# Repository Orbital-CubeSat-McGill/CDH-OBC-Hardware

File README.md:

# CDH-OBC-Hardware
On Board Computer for Command and Data Handling.

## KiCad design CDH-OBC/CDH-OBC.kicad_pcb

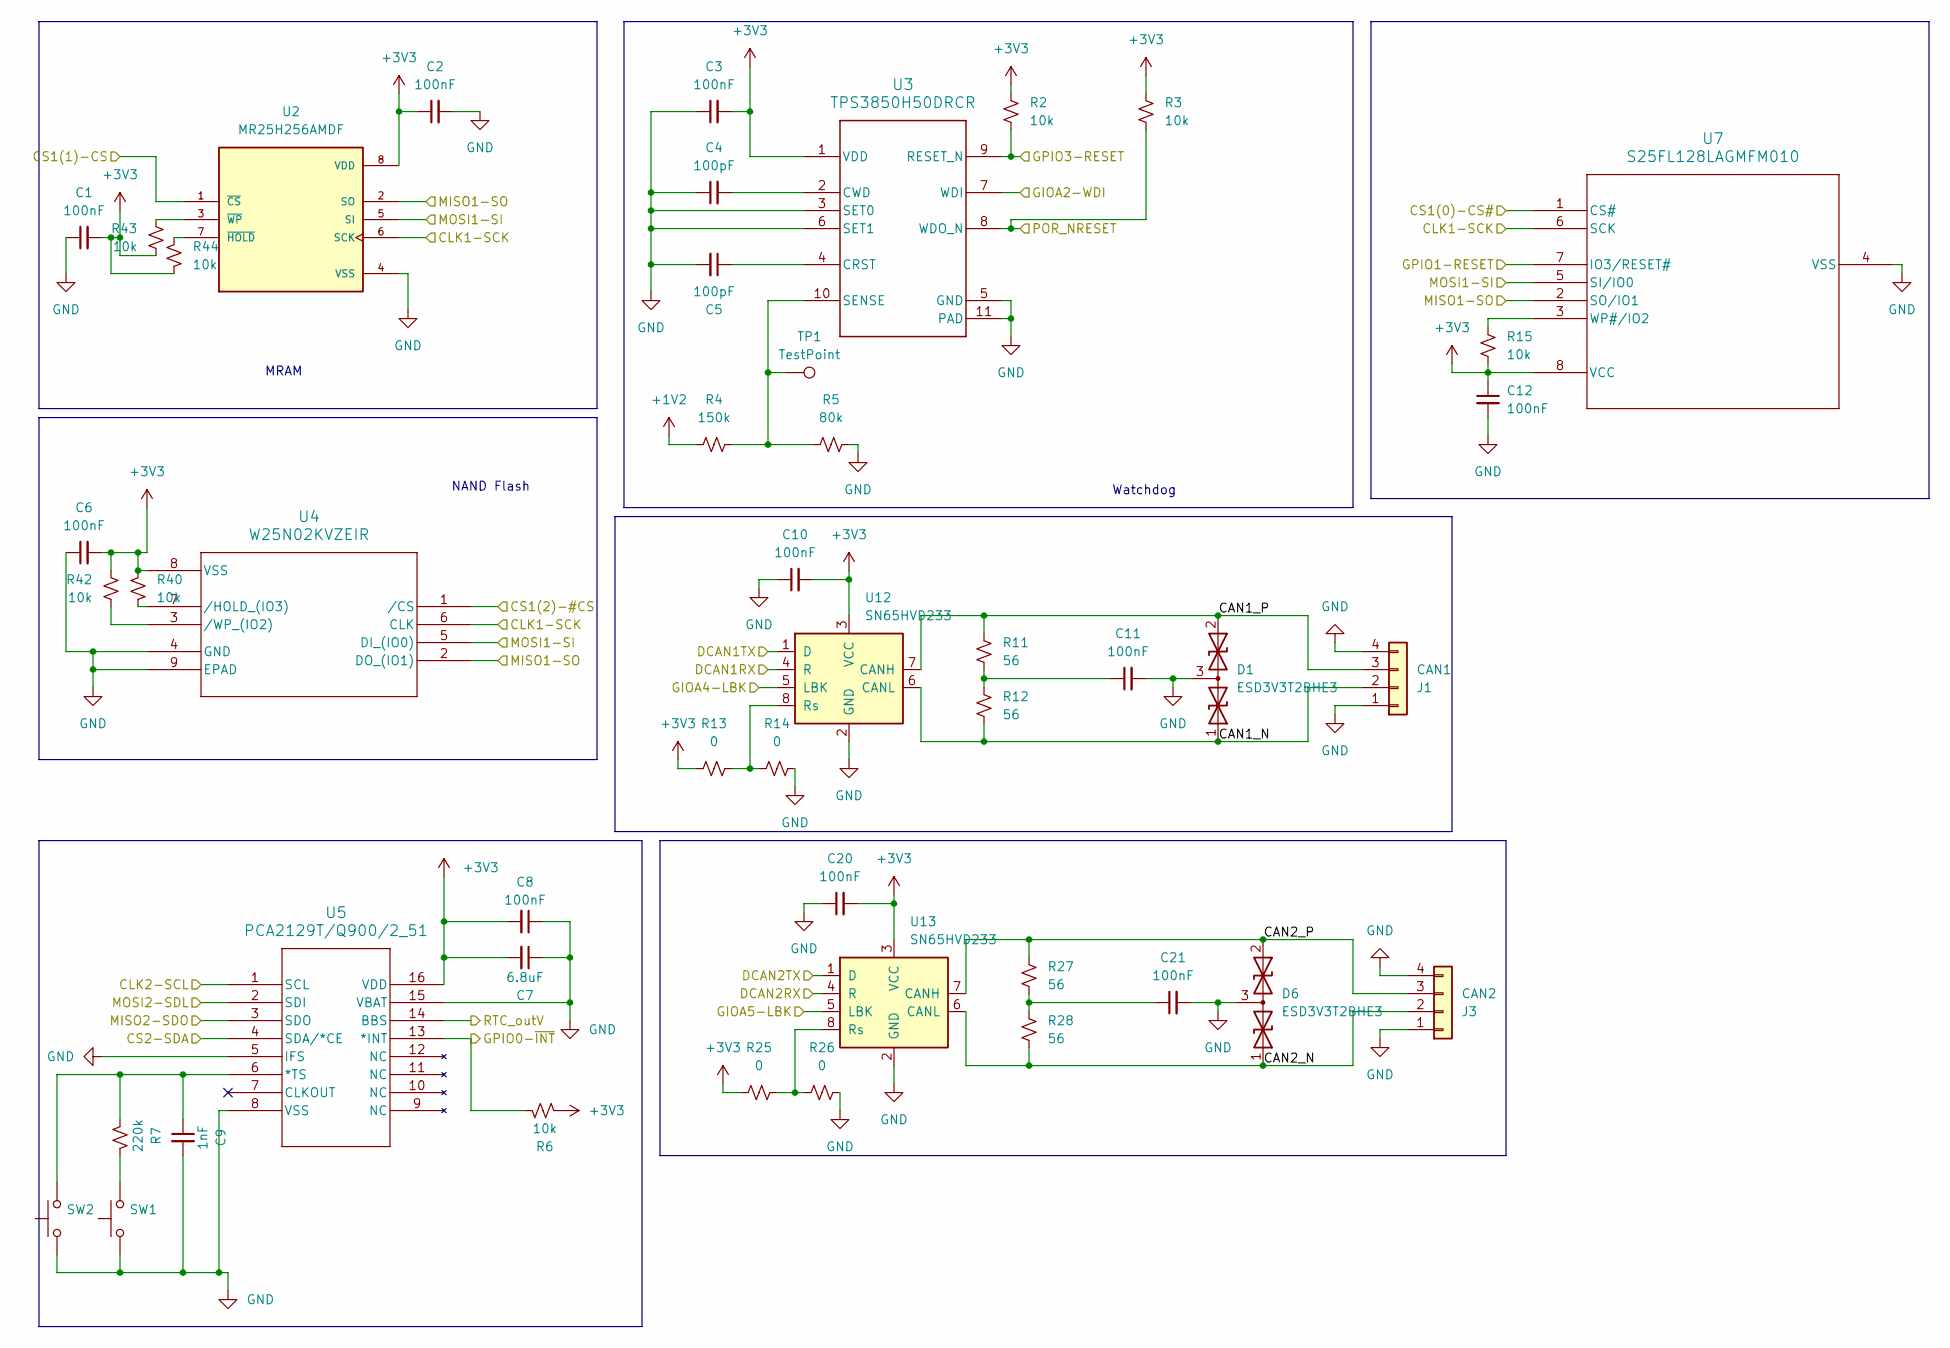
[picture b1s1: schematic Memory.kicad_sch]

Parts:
C1, C2, C3, C6, C8, C10, C11, C12, C20, C21: 100nF; C_0603_1608Metric
C4, C5: 100pF; C_0603_1608Metric
C7: 6.8uF; C_0603_1608Metric
C9: 1nF; C_0603_1608Metric
D1, D6: ESD3V3T2BHE3; SOT-23
J1: CAN1; JST_SH_SM04B-SRSS-TB_1x04-1MP_P1.00mm_Horizontal
J3: CAN2; JST_SH_SM04B-SRSS-TB_1x04-1MP_P1.00mm_Horizontal
R2, R3, R6, R15, R40, R42, R43, R44: 10k; R_0603_1608Metric
R4: 150k; R_0603_1608Metric
R5: 80k; R_0603_1608Metric
R7: 220k; R_0603_1608Metric
R11, R12, R27, R28: 56; R_0603_1608Metric
R13, R14, R25, R26: 0; R_0603_1608Metric
SW1, SW2: SW_Push; SW_TL3315NF250Q
TP1: TestPoint; TestPoint_Pad_D1.0mm
U2: MR25H256AMDF; SON127P500X600X90-9N; PARTREV 12.6
U3: TPS3850H50DRCR; DRC0010J
U4: W25N02KVZEIR; SON_WSON8_ZE_WIN
U5: PCA2129T/Q900/2_51; SO16_SOT162-1_NXP
U7: S25FL128LAGMFM010; SOIC8_INF
U12, U13: SN65HVD233; SOIC-8_3.9x4.9mm_P1.27mm

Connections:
+1V2: R4.1; also elsewhere on the board
+3V3: C1.2, C2.1, C3.2, C6.2, C7.2, C8.2, C10.2, C12.1, C20.2, R2.1, R3.1, R6.2, R13.1, R15.2, R25.1, R40.1, R42.1, R43.2, R44.2, U2.8 (VDD), U3.1 (VDD), U4.8 (VSS), U5.16 (VDD), U7.8 (VCC), U12.3 (VCC), U13.3 (VCC); also elsewhere on the board
/Memory ICs/CAN1_N: D1.1 (A1), J1.2, R12.2, U12.6 (CANL)
/Memory ICs/CAN1_P: D1.2 (A2), J1.3, R11.1, U12.7 (CANH)
/Memory ICs/CAN2_N: D6.1 (A1), J3.2, R28.2, U13.6 (CANL)
/Memory ICs/CAN2_P: D6.2 (A2), J3.3, R27.1, U13.7 (CANH)
/Memory ICs/CLK1-SCK: U2.6 (SCK), U4.6 (CLK), U7.6 (SCK); also elsewhere on the board
/Memory ICs/CLK2-SCL: U5.1 (SCL); also elsewhere on the board
/Memory ICs/CS1(0)-CS#: U7.1 (CS#); also elsewhere on the board
/Memory ICs/CS1(1)-CS: U2.1 (~CS); also elsewhere on the board
/Memory ICs/CS1(2)-#CS: U4.1 (/CS); also elsewhere on the board
/Memory ICs/CS2-SDA: U5.4 (SDA/*CE); also elsewhere on the board
/Memory ICs/DCAN1RX: U12.4 (R); also elsewhere on the board
/Memory ICs/DCAN1TX: U12.1 (D); also elsewhere on the board
/Memory ICs/DCAN2RX: U13.4 (R); also elsewhere on the board
/Memory ICs/DCAN2TX: U13.1 (D); also elsewhere on the board
/Memory ICs/GIOA2-WDI: U3.7 (WDI); also elsewhere on the board
/Memory ICs/GIOA4-LBK: U12.5 (LBK); also elsewhere on the board
/Memory ICs/GIOA5-LBK: U13.5 (LBK); also elsewhere on the board
/Memory ICs/GPIO0-~INT: R6.1, U5.13 (*INT); also elsewhere on the board
/Memory ICs/GPIO1-RESET: U7.7 (IO3/RESET#); also elsewhere on the board
/Memory ICs/GPIO3-RESET: R2.2, U3.9 (RESET_N); also elsewhere on the board
/Memory ICs/MISO1-SO: U2.2 (SO), U4.2 (DO_(IO1)), U7.2 (SO/IO1); also elsewhere on the board
/Memory ICs/MISO2-SDO: U5.3 (SDO); also elsewhere on the board
/Memory ICs/MOSI1-SI: U2.5 (SI), U4.5 (DI_(IO0)), U7.5 (SI/IO0); also elsewhere on the board
/Memory ICs/MOSI2-SDL: U5.2 (SDI); also elsewhere on the board
/Memory ICs/POR_NRESET: R3.2, U3.8 (WDO_N); also elsewhere on the board
/Memory ICs/RTC_outV: U5.14 (BBS); also elsewhere on the board
GND: C1.1, C2.2, C3.1, C4.1, C5.2, C6.1, C7.1, C8.1, C9.2, C10.1, C11.2, C12.2, C20.1, C21.2, D1.3 (common), D6.3 (common), J1.1, J1.4, J3.1, J3.4, R5.2, R14.2, R26.2, SW1.1, SW2.1, U2.4 (VSS), U2.9 (VSS), U3.3 (SET0), U3.5 (GND), U3.6 (SET1), U3.11 (PAD), U4.4 (GND), U4.9 (EPAD), U5.5 (IFS), U5.8 (VSS), U5.15 (VBAT), U7.4 (VSS), U12.2 (GND), U13.2 (GND); also elsewhere on the board
unnamed: C11.1, R11.2, R12.1
unnamed: C21.1, R27.2, R28.1
unnamed: R7.1, SW1.2
unnamed: R44.1, U2.7 (~HOLD)
unnamed: R43.1, U2.3 (~WP)
unnamed: C5.1, U3.4 (CRST)
unnamed: C4.2, U3.2 (CWD)
unnamed: R4.2, R5.1, TP1.1 (1_1), U3.10 (SENSE)
unnamed: R40.2, U4.7 (/HOLD_(IO3))
unnamed: R42.2, U4.3 (/WP_(IO2))
unnamed: C9.1, R7.2, SW2.2, U5.6 (*TS)
unnamed: R15.1, U7.3 (WP#/IO2)
unnamed: R13.2, R14.1, U12.8 (Rs)
unnamed: R25.2, R26.1, U13.8 (Rs)

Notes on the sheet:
NAND Flash
Watchdog
MRAM

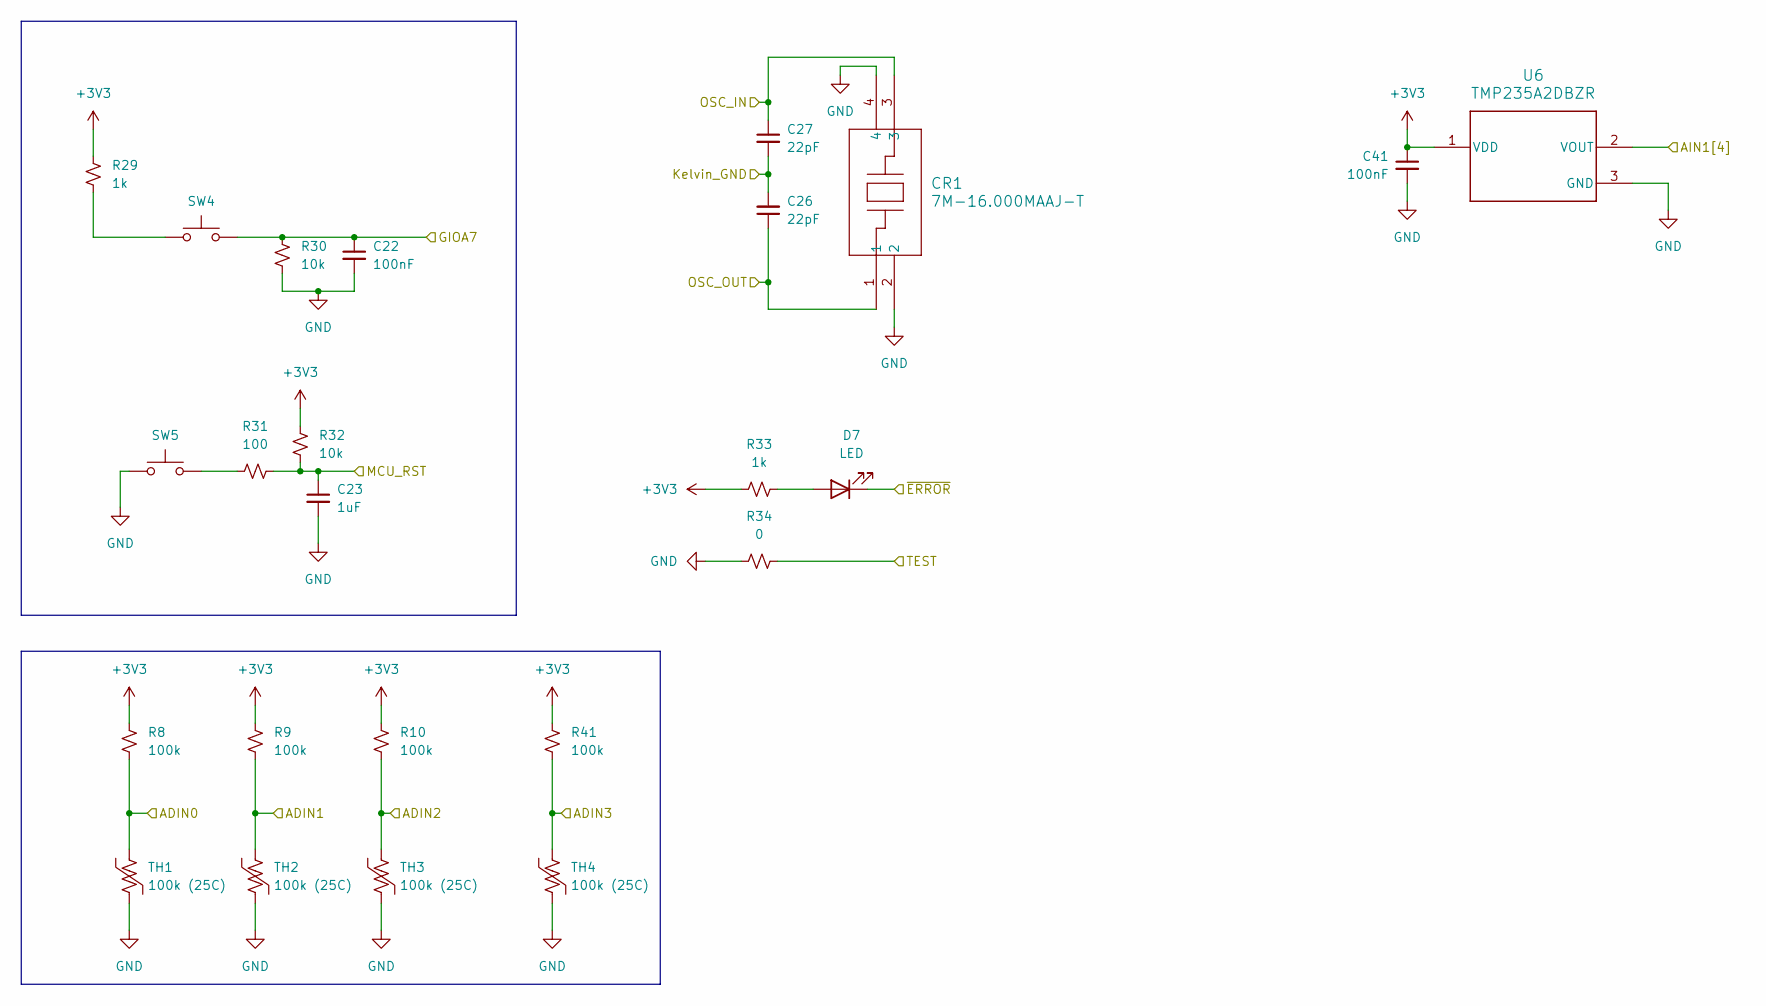
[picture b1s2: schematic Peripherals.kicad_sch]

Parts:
C22, C41: 100nF; C_0603_1608Metric
C23: 1uF; C_0603_1608Metric
C26, C27: 22pF; C_0603_1608Metric
CR1: 7M-16.000MAAJ-T; CRYSTAL_TXC_7M
D7: LED; LED_0603_1608Metric
R8, R9, R10, R41: 100k; R_0603_1608Metric
R29, R33: 1k; R_0603_1608Metric
R30, R32: 10k; R_0603_1608Metric
R31: 100; R_0603_1608Metric
R34: 0; R_0603_1608Metric
SW4, SW5: SW_Push; SW_TL3315NF250Q
TH1, TH2, TH3, TH4: 100k (25C); R_0603_1608Metric
U6: TMP235A2DBZR; DBZ0003A-MFG

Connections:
+3V3: C41.1, R8.1, R9.1, R10.1, R29.2, R32.1, R33.1, R41.1, U6.1 (VDD); also elsewhere on the board
/MCU peripherals/ADIN0: R8.2, TH1.1; also elsewhere on the board
/MCU peripherals/ADIN1: R9.2, TH2.1; also elsewhere on the board
/MCU peripherals/ADIN2: R10.2, TH3.1; also elsewhere on the board
/MCU peripherals/ADIN3: R41.2, TH4.1; also elsewhere on the board
/MCU peripherals/AIN1[4]: U6.2 (VOUT); also elsewhere on the board
/MCU peripherals/GIOA7: C22.1, R30.1, SW4.2; also elsewhere on the board
/MCU peripherals/Kelvin_GND: C26.2, C27.2; also elsewhere on the board
/MCU peripherals/MCU_RST: C23.1, R31.2, R32.2; also elsewhere on the board
/MCU peripherals/OSC_IN: C27.1, CR1.3; also elsewhere on the board
/MCU peripherals/OSC_OUT: C26.1, CR1.1; also elsewhere on the board
/MCU peripherals/TEST: R34.2; also elsewhere on the board
/MCU peripherals/~ERROR: D7.1 (K); also elsewhere on the board
GND: C22.2, C23.2, C41.2, CR1.2, CR1.4, R30.2, R34.1, SW5.1, TH1.2, TH2.2, TH3.2, TH4.2, U6.3 (GND); also elsewhere on the board
unnamed: D7.2 (A), R33.2
unnamed: R29.1, SW4.1
unnamed: R31.1, SW5.2

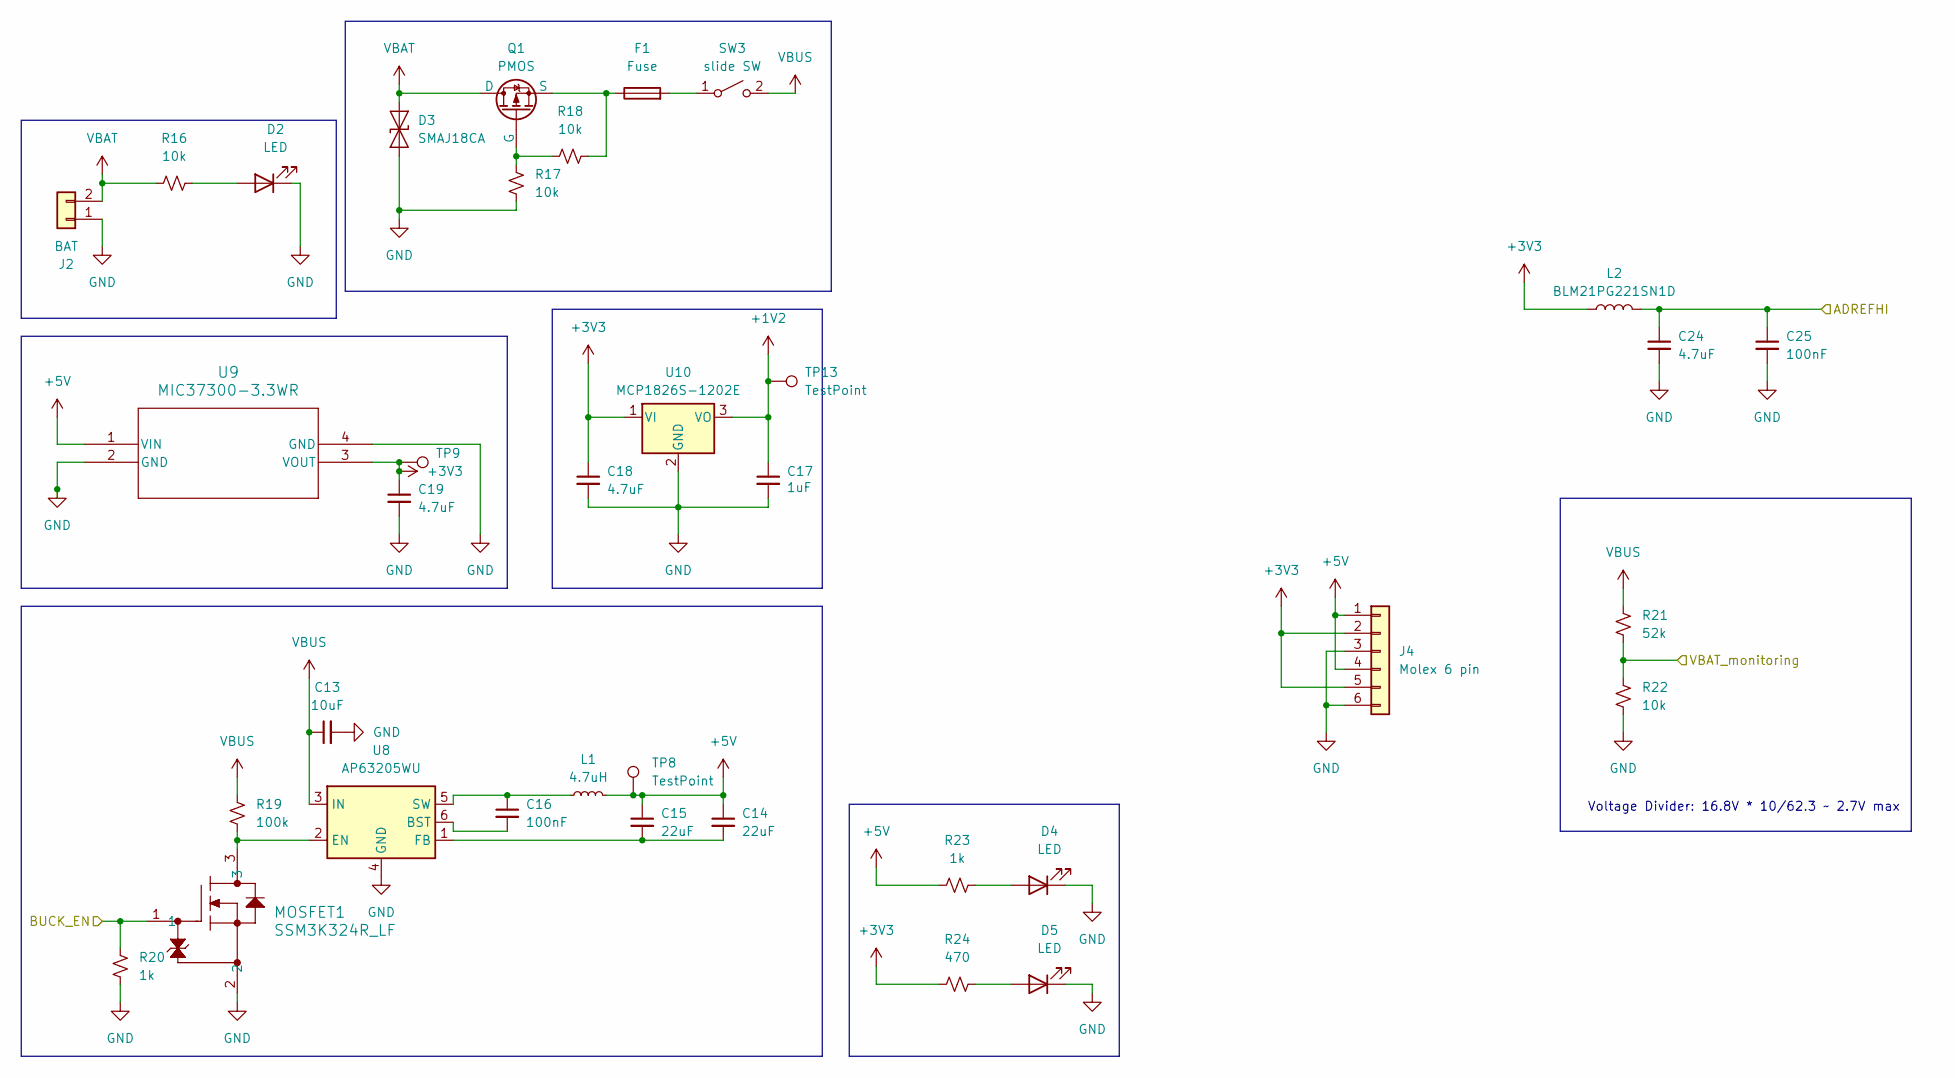
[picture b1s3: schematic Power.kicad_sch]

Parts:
C13: 10uF; C_0603_1608Metric
C14, C15: 22uF; C_0603_1608Metric
C16, C25: 100nF; C_0603_1608Metric
C17: 1uF; C_0603_1608Metric
C18, C19, C24: 4.7uF; C_0603_1608Metric
D2, D4, D5: LED; LED_0603_1608Metric
D3: SMAJ18CA; D_SMA
F1: Fuse; Fuse_0805_2012Metric
J2: BAT; AMASS_XT60IPW-M_1x03_P7.20mm_Horizontal
J4: Molex 6 pin; Molex_Micro-Fit_3.0_43045-0600_2x03_P3.00mm_Horizontal
L1: 4.7uH; L_Sunlord_SWPA5040S
L2: BLM21PG221SN1D; L_0805_2012Metric
MOSFET1: SSM3K324R_LF; TSOT-23
Q1: PMOS; TSOT-23
R16, R17, R18, R22: 10k; R_0603_1608Metric
R19: 100k; R_0603_1608Metric
R20, R23: 1k; R_0603_1608Metric
R21: 52k; R_0603_1608Metric
R24: 470; R_0603_1608Metric
SW3: slide SW; SW_GF-123-0054
TP8, TP9, TP13: TestPoint; TestPoint_Pad_D1.0mm
U8: AP63205WU; TSOT-23-6
U9: MIC37300-3.3WR; SPAK-3LD-PL-1_MCH
U10: MCP1826S-1202E; SOT-223_3MC_MCH

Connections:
+1V2: C17.1, TP13.1 (1_1), U10.3 (VO); also elsewhere on the board
+3V3: C18.1, C19.1, J4.2, J4.5, L2.1, R24.1, TP9.1 (1_1), U9.3 (VOUT), U10.1 (VI); also elsewhere on the board
+5V: C14.1, C15.1, J4.1, J4.4, L1.2, R23.1, TP8.1 (1_1), U9.1 (VIN)
/MicroController/AD1IN[5]: R21.2, R22.1; also elsewhere on the board
/MicroController/ADREFHI: C24.1, C25.1, L2.2; also elsewhere on the board
/MicroController/BUCK_EN: MOSFET1.1, R20.1; also elsewhere on the board
GND: C13.2, C17.2, C18.2, C19.2, C24.2, C25.2, D2.1 (K), D3.1 (A1), D4.1 (K), D5.1 (K), J2.1, J4.3, J4.6, MOSFET1.2, R17.2, R20.2, R22.2, U8.4 (GND), U9.2 (GND), U9.4 (GND), U10.2 (GND); also elsewhere on the board
unnamed: D2.2 (A), R16.2
unnamed: D4.2 (A), R23.2
unnamed: D5.2 (A), R24.2
unnamed: Q1.2 (G), R17.1, R18.1
unnamed: F1.1, Q1.3 (S), R18.2
unnamed: F1.2, SW3.1 (A)
unnamed: C16.2, U8.6 (BST)
unnamed: MOSFET1.3, R19.2, U8.2 (EN)
unnamed: C14.2, C15.2, U8.1 (FB)
unnamed: C16.1, L1.1, U8.5 (SW)
VBAT: D3.2 (A2), J2.2, Q1.1 (D), R16.1
VBUS: C13.1, R19.1, R21.1, SW3.2 (B), U8.3 (IN)

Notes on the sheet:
Voltage Divider: 16.8V * 10/62.3 ~ 2.7V max

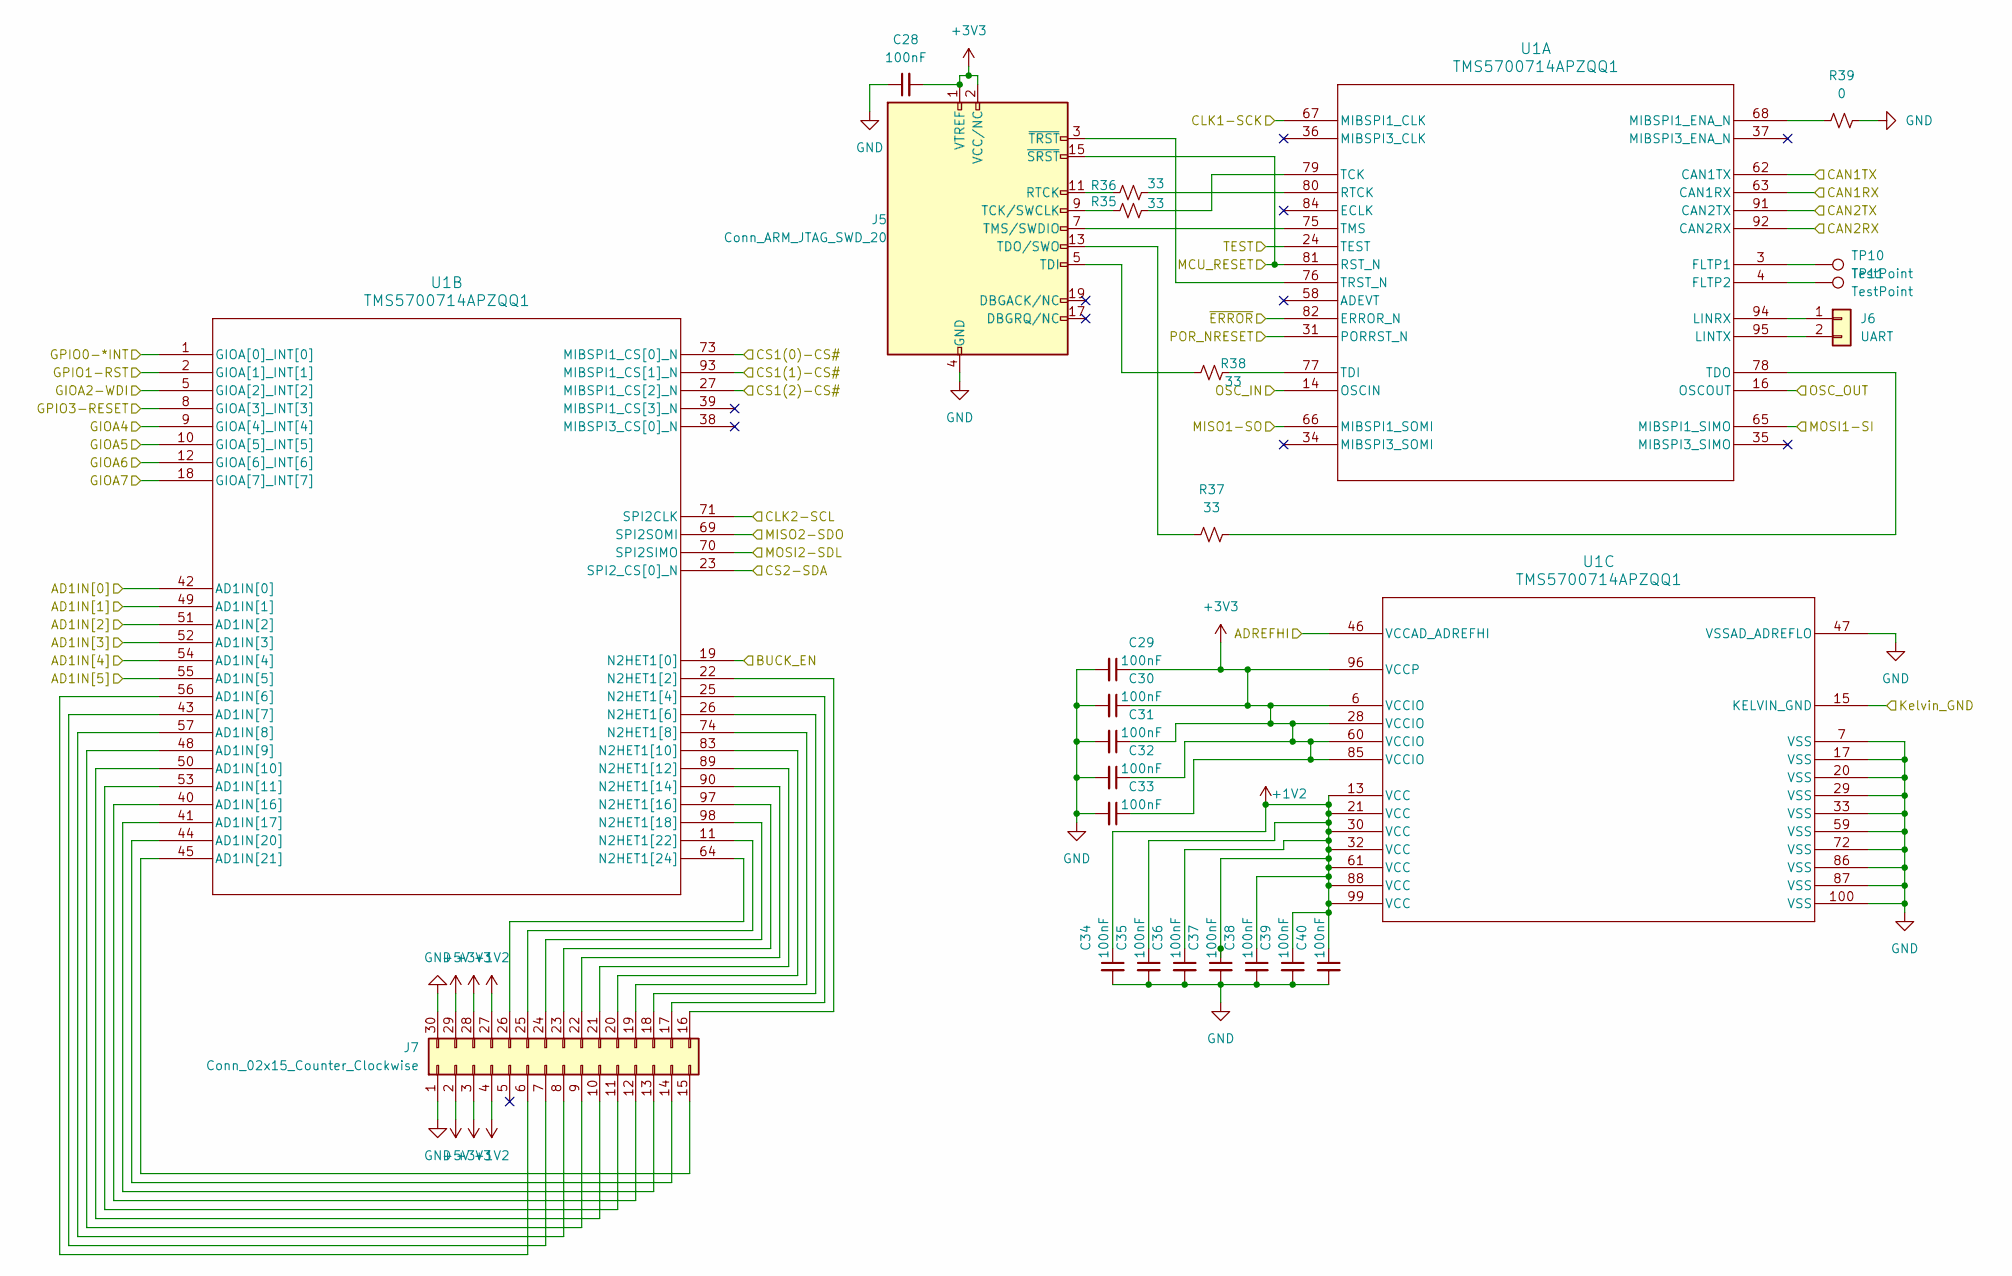
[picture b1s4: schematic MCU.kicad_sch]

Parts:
C28, C29, C30, C31, C32, C33, C34, C35, C36, C37, C38, C39, C40: 100nF; C_0603_1608Metric
J5: Conn_ARM_JTAG_SWD_20; PinHeader_2x10_P2.54mm_Vertical
J6: UART; PinHeader_1x02_P2.54mm_Vertical
J7: Conn_02x15_Counter_Clockwise; PinHeader_2x15_P2.54mm_Vertical
R35, R36, R37, R38: 33; R_0603_1608Metric
R39: 0; R_0603_1608Metric
TP10, TP11: TestPoint; TestPoint_Pad_D1.0mm
U1: TMS5700714APZQQ1; PZ0100A_N

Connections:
+1V2: C34.1, C35.1, C36.1, C37.1, C38.1, C39.1, C40.1, J7.4, J7.27, U1.13 (VCC), U1.21 (VCC), U1.30 (VCC), U1.32 (VCC), U1.61 (VCC), U1.88 (VCC), U1.99 (VCC); also elsewhere on the board
+3V3: C28.2, C29.1, C30.1, C31.1, C32.1, C33.1, J5.1 (VTREF), J5.2 (VCC/NC), J7.3, J7.28, U1.6 (VCCIO), U1.28 (VCCIO), U1.60 (VCCIO), U1.85 (VCCIO), U1.96 (VCCP); also elsewhere on the board
/MCU peripherals/ADIN0: U1.42 (AD1IN[0]); also elsewhere on the board
/MCU peripherals/ADIN1: U1.49 (AD1IN[1]); also elsewhere on the board
/MCU peripherals/ADIN2: U1.51 (AD1IN[2]); also elsewhere on the board
/MCU peripherals/ADIN3: U1.52 (AD1IN[3]); also elsewhere on the board
/MCU peripherals/AIN1[4]: U1.54 (AD1IN[4]); also elsewhere on the board
/MCU peripherals/GIOA7: U1.18 (GIOA[7]_INT[7]); also elsewhere on the board
/MCU peripherals/Kelvin_GND: U1.15 (KELVIN_GND); also elsewhere on the board
/MCU peripherals/MCU_RST: J5.15 (~SRST), U1.81 (RST_N); also elsewhere on the board
/MCU peripherals/OSC_IN: U1.14 (OSCIN); also elsewhere on the board
/MCU peripherals/OSC_OUT: U1.16 (OSCOUT); also elsewhere on the board
/MCU peripherals/TEST: U1.24 (TEST); also elsewhere on the board
/MCU peripherals/~ERROR: U1.82 (ERROR_N); also elsewhere on the board
/Memory ICs/CLK1-SCK: U1.67 (MIBSPI1_CLK); also elsewhere on the board
/Memory ICs/CLK2-SCL: U1.71 (SPI2CLK); also elsewhere on the board
/Memory ICs/CS1(0)-CS#: U1.73 (MIBSPI1_CS[0]_N); also elsewhere on the board
/Memory ICs/CS1(1)-CS: U1.93 (MIBSPI1_CS[1]_N); also elsewhere on the board
/Memory ICs/CS1(2)-#CS: U1.27 (MIBSPI1_CS[2]_N); also elsewhere on the board
/Memory ICs/CS2-SDA: U1.23 (SPI2_CS[0]_N); also elsewhere on the board
/Memory ICs/DCAN1RX: U1.63 (CAN1RX); also elsewhere on the board
/Memory ICs/DCAN1TX: U1.62 (CAN1TX); also elsewhere on the board
/Memory ICs/DCAN2RX: U1.92 (CAN2RX); also elsewhere on the board
/Memory ICs/DCAN2TX: U1.91 (CAN2TX); also elsewhere on the board
/Memory ICs/GIOA2-WDI: U1.5 (GIOA[2]_INT[2]); also elsewhere on the board
/Memory ICs/GIOA4-LBK: U1.10 (GIOA[5]_INT[5]); also elsewhere on the board
/Memory ICs/GIOA5-LBK: U1.9 (GIOA[4]_INT[4]); also elsewhere on the board
/Memory ICs/GPIO0-~INT: U1.1 (GIOA[0]_INT[0]); also elsewhere on the board
/Memory ICs/GPIO1-RESET: U1.2 (GIOA[1]_INT[1]); also elsewhere on the board
/Memory ICs/GPIO3-RESET: U1.8 (GIOA[3]_INT[3]); also elsewhere on the board
/Memory ICs/MISO1-SO: U1.66 (MIBSPI1_SOMI); also elsewhere on the board
/Memory ICs/MISO2-SDO: U1.69 (SPI2SOMI); also elsewhere on the board
/Memory ICs/MOSI1-SI: U1.65 (MIBSPI1_SIMO); also elsewhere on the board
/Memory ICs/MOSI2-SDL: U1.70 (SPI2SIMO); also elsewhere on the board
/Memory ICs/POR_NRESET: U1.31 (PORRST_N); also elsewhere on the board
/Memory ICs/RTC_outV: U1.12 (GIOA[6]_INT[6]); also elsewhere on the board
/MicroController/AD1IN[5]: U1.55 (AD1IN[5]); also elsewhere on the board
/MicroController/ADREFHI: U1.46 (VCCAD_ADREFHI); also elsewhere on the board
/MicroController/BUCK_EN: U1.19 (N2HET1[0]); also elsewhere on the board
GND: C28.1, C29.2, C30.2, C31.2, C32.2, C33.2, C34.2, C35.2, C36.2, C37.2, C38.2, C39.2, C40.2, J5.4 (GND), J5.6 (GND), J5.8 (GND), J5.10 (GND), J5.12 (GND), J5.14 (GND), J5.16 (GND), J5.18 (GND), J5.20 (GND), J7.1, J7.30, R39.2, U1.7 (VSS), U1.17 (VSS), U1.20 (VSS), U1.29 (VSS), U1.33 (VSS), U1.47 (VSSAD_ADREFLO), U1.59 (VSS), U1.72 (VSS), U1.86 (VSS), U1.87 (VSS), U1.100 (VSS); also elsewhere on the board
unnamed: J5.11 (RTCK), R36.1
unnamed: J5.9 (TCK/SWCLK), R35.1
unnamed: J5.5 (TDI), R38.1
unnamed: J5.13 (TDO/SWO), R37.1
unnamed: J5.7 (TMS/SWDIO), U1.75 (TMS)
unnamed: J5.3 (~TRST), U1.76 (TRST_N)
unnamed: J6.1, U1.94 (LINRX)
unnamed: J6.2, U1.95 (LINTX)
unnamed: J7.2, J7.29
unnamed: J7.6, U1.56 (AD1IN[6])
unnamed: J7.7, U1.43 (AD1IN[7])
unnamed: J7.8, U1.57 (AD1IN[8])
unnamed: J7.9, U1.48 (AD1IN[9])
unnamed: J7.10, U1.50 (AD1IN[10])
unnamed: J7.11, U1.53 (AD1IN[11])
unnamed: J7.12, U1.40 (AD1IN[16])
unnamed: J7.13, U1.41 (AD1IN[17])
unnamed: J7.14, U1.44 (AD1IN[20])
unnamed: J7.15, U1.45 (AD1IN[21])
unnamed: J7.16, U1.22 (N2HET1[2])
unnamed: J7.17, U1.25 (N2HET1[4])
unnamed: J7.18, U1.26 (N2HET1[6])
unnamed: J7.19, U1.74 (N2HET1[8])
unnamed: J7.20, U1.83 (N2HET1[10])
unnamed: J7.21, U1.89 (N2HET1[12])
unnamed: J7.22, U1.90 (N2HET1[14])
unnamed: J7.23, U1.97 (N2HET1[16])
unnamed: J7.24, U1.98 (N2HET1[18])
unnamed: J7.25, U1.11 (N2HET1[22])
unnamed: J7.26, U1.64 (N2HET1[24])
unnamed: TP10.1 (1_1), U1.3 (FLTP1)
unnamed: TP11.1 (1_1), U1.4 (FLTP2)
unnamed: R39.1, U1.68 (MIBSPI1_ENA_N)
unnamed: R36.2, U1.80 (RTCK)
unnamed: R35.2, U1.79 (TCK)
unnamed: R38.2, U1.77 (TDI)
unnamed: R37.2, U1.78 (TDO)

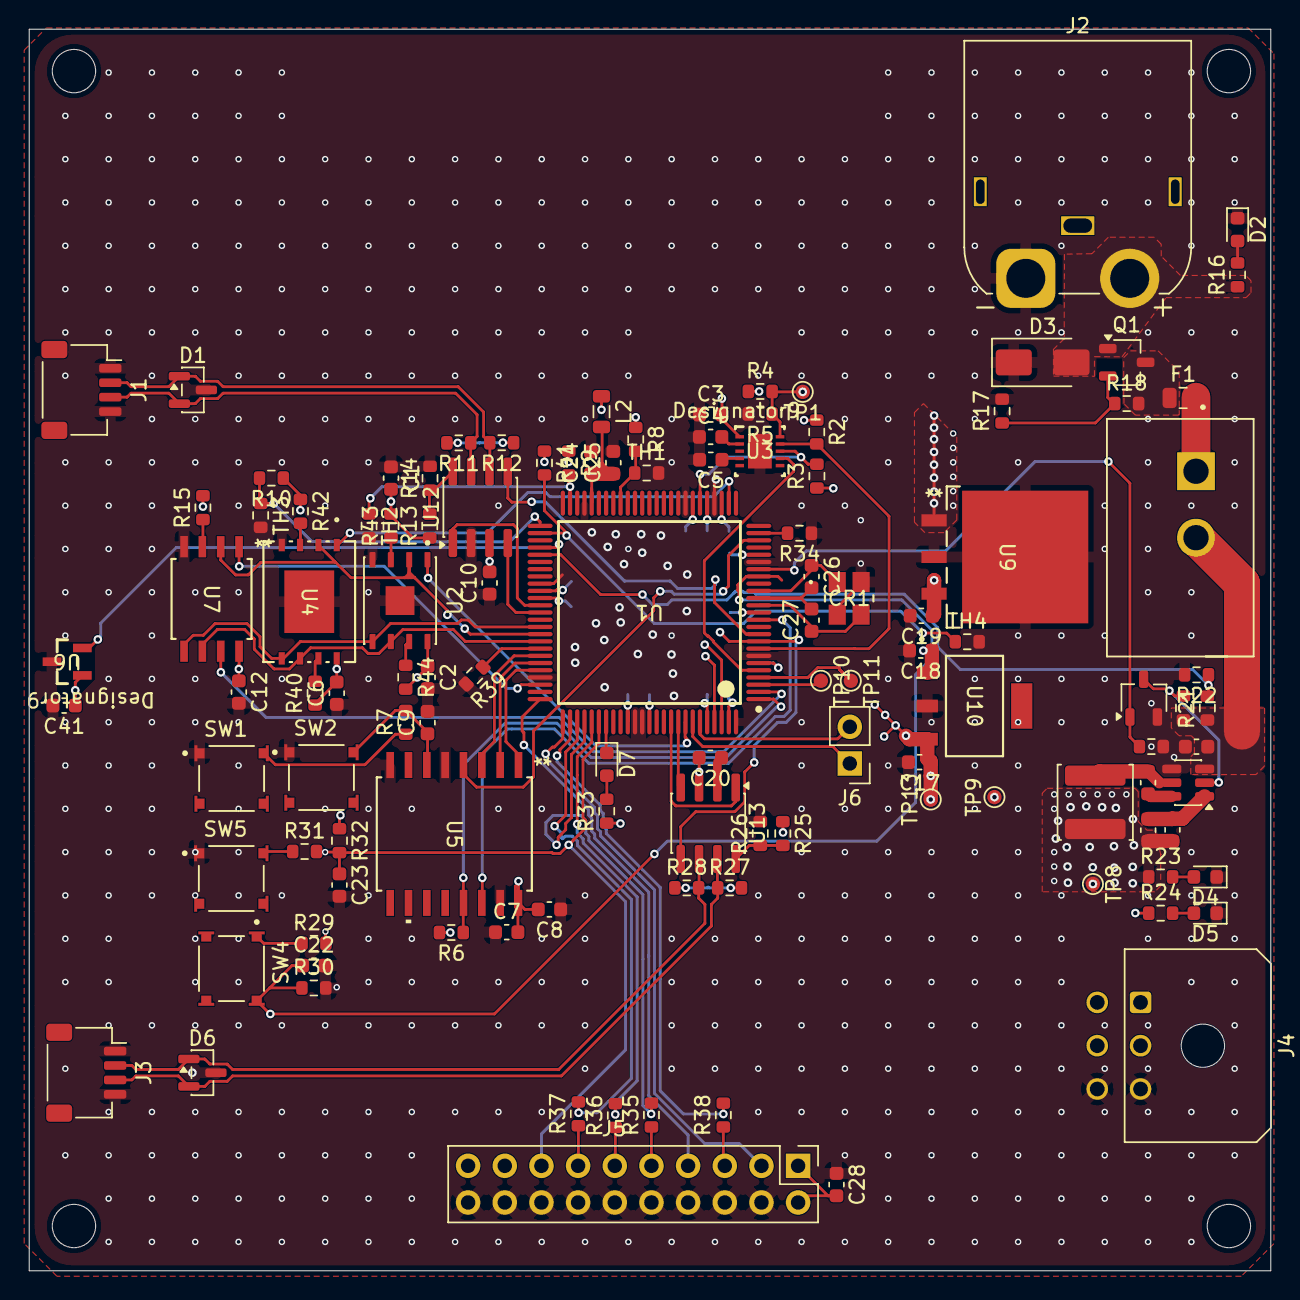
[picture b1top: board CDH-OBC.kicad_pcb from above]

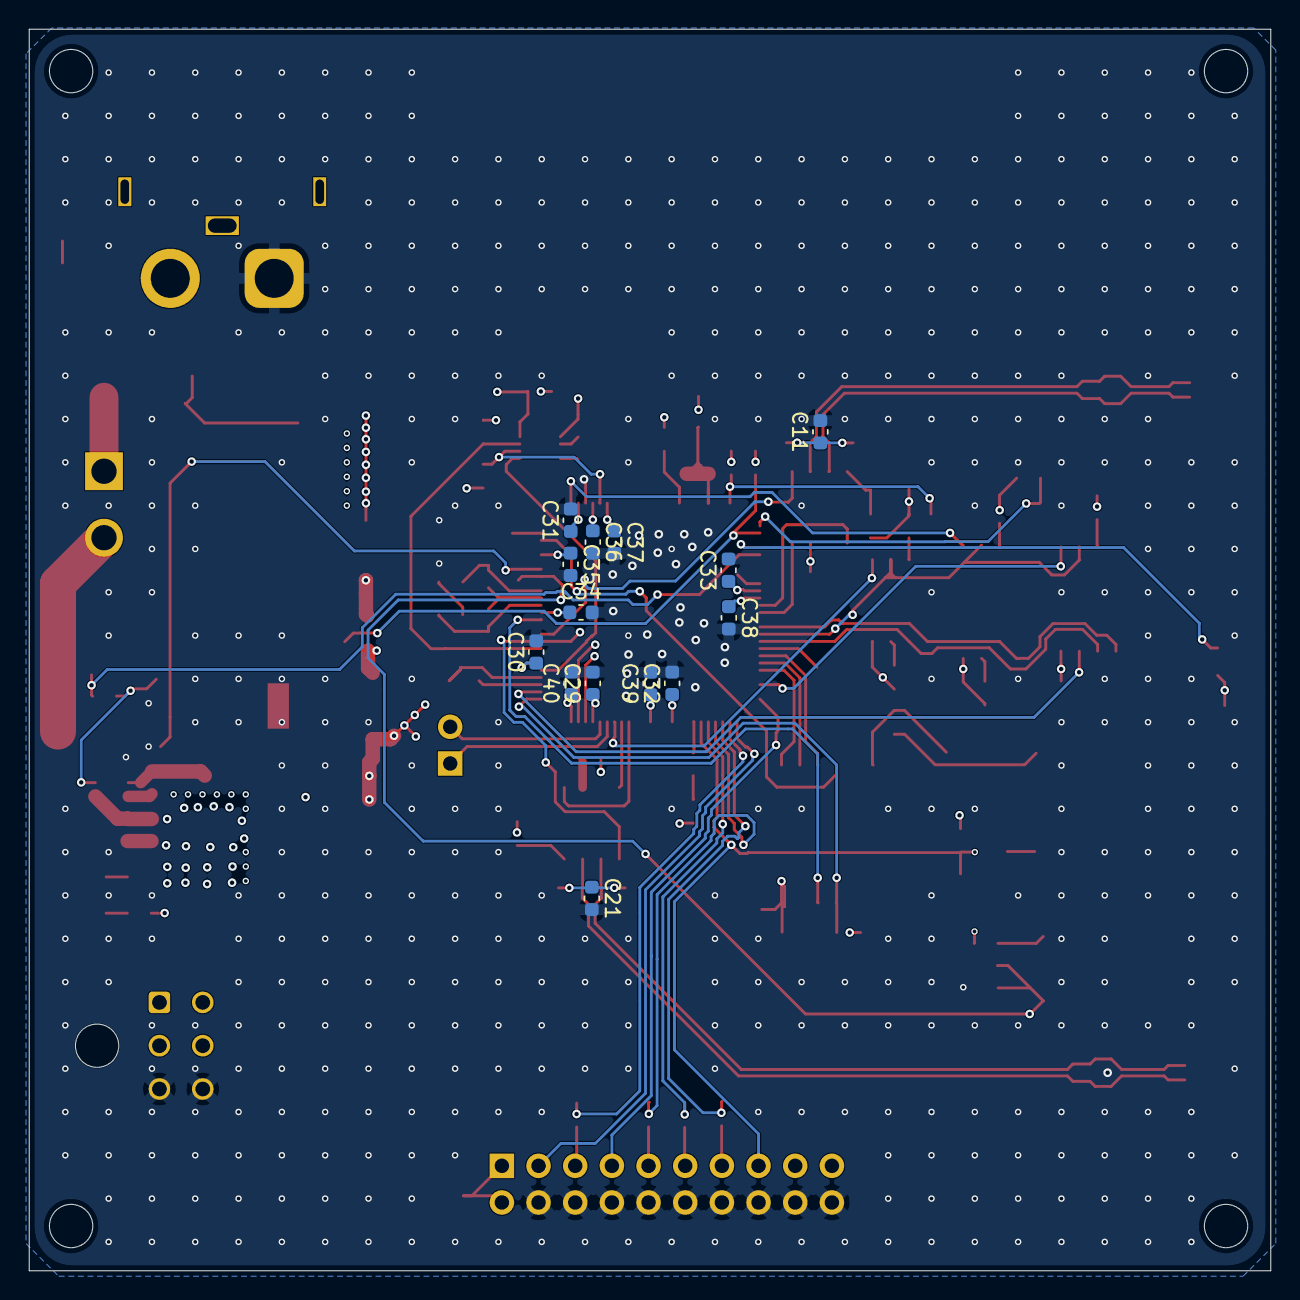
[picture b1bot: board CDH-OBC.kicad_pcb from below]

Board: 4 copper layers, 86.0 x 86.0 mm, 130 parts (14 on the bottom side), 89 nets.
